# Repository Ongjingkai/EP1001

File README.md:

# EP1001
Just do things before they start to save you the time and effort

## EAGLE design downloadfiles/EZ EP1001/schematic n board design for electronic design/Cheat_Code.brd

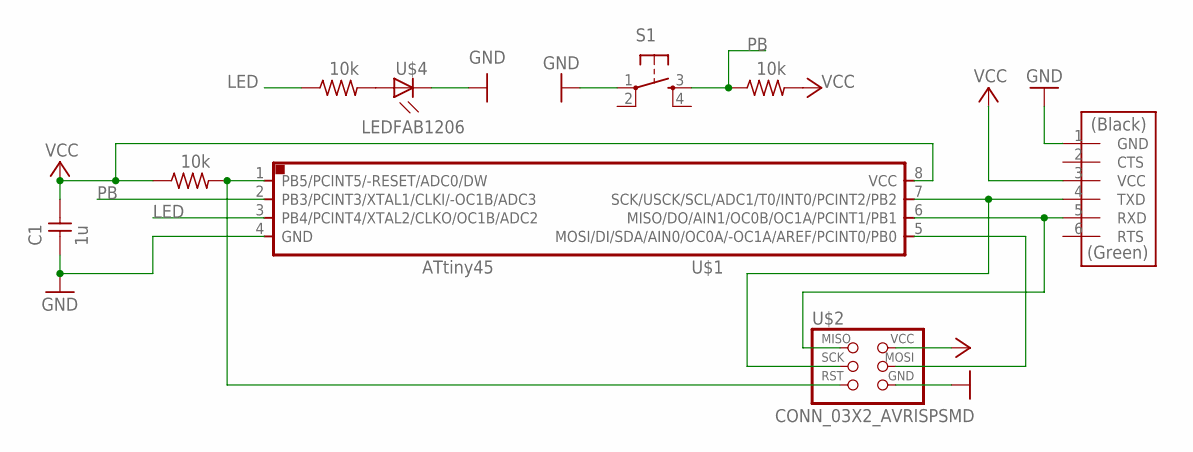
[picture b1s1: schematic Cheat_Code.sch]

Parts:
C1: 1u; C1206FAB
R1, R2, R3: 10k; R1206
S1: SW_SWITCH_TACTILE_6MM6MM_SWITCH; 6MM_SWITCH
U$1: UC_ATTINY45SI; SOIC8
U$2: CONN_03X2_AVRISPSMD; 2X03SMD
U$3: CONN_06_FTDI-SMD-HEADER; 1X06SMD
U$4: LEDFAB1206; LED1206FAB

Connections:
GND: C1.1, S1.1, U$1.4 (GND), U$2.6 (GND), U$3.1 (GND), U$4.2 (C)
LED: R3.1, U$1.3 (PB4/PCINT4/XTAL2/CLKO/OC1B/ADC2)
unnamed: U$1.6 (MISO/DO/AIN1/OC0B/OC1A/PCINT1/PB1), U$2.1 (MISO), U$3.5 (RXD)
unnamed: U$1.7 (SCK/USCK/SCL/ADC1/T0/INT0/PCINT2/PB2), U$2.3 (SCK), U$3.4 (TXD)
unnamed: R2.2, U$1.1 (PB5/PCINT5/-RESET/ADC0/DW), U$2.5 (RST)
unnamed: U$1.5 (MOSI/DI/SDA/AIN0/OC0A/-OC1A/AREF/PCINT0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), U$2.4 (MOSI)
unnamed: R3.2, U$4.1 (A)
PB: R1.1, S1.3 (S), U$1.2 (PB3/PCINT3/XTAL1/CLKI/-OC1B/ADC3)
VCC: C1.2, R1.2, R2.1, U$1.8 (VCC), U$2.2 (VCC), U$3.3 (VCC)

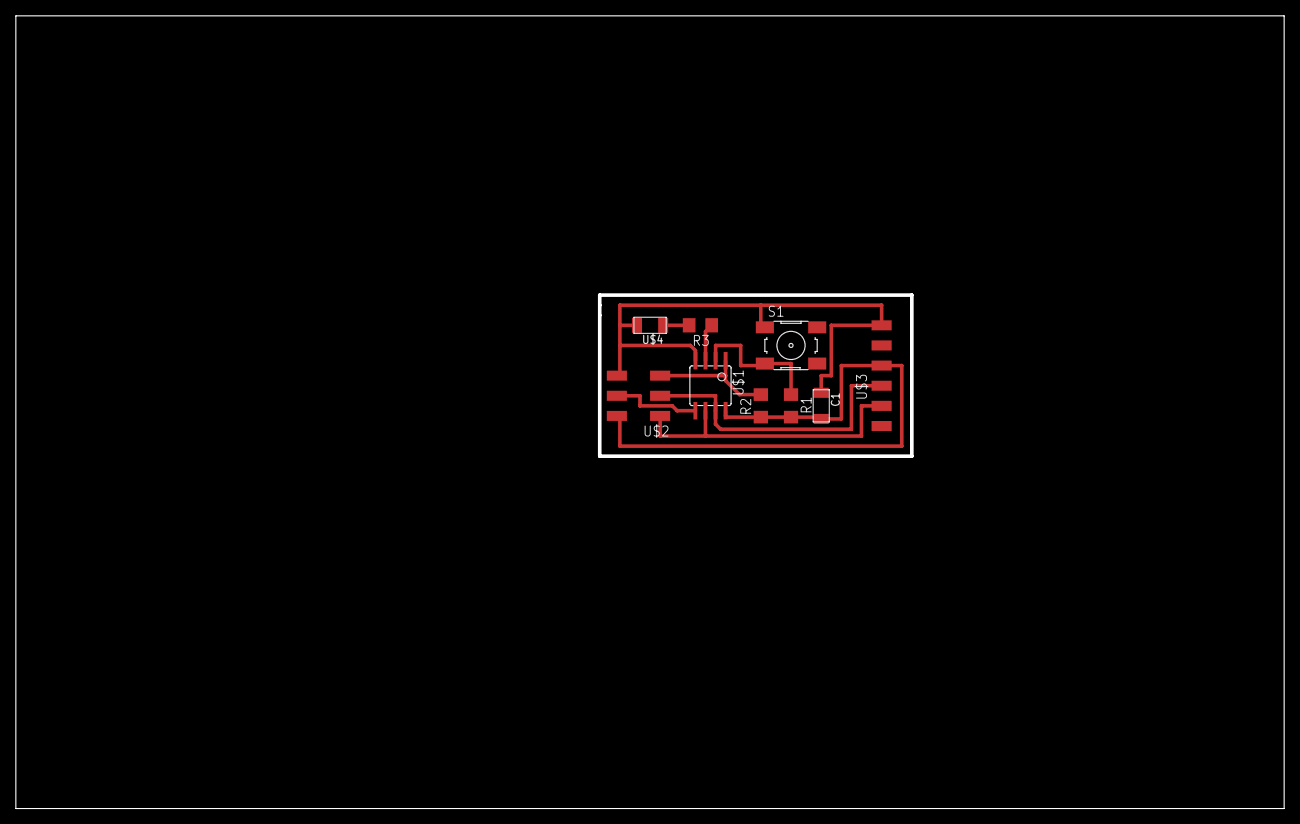
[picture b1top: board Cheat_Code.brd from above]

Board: 2 copper layers, 160.0 x 100.0 mm, 9 parts (0 on the bottom side), 9 nets.

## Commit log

2022-05-15 The Start of it all
2022-05-16 fablab safety shit
2022-10-05 deez
    nutz
2022-10-14 lazy mode
2022-10-21 Added Download files
2022-10-28 Slight update
2022-10-29 added soldering to electronic production
2022-10-30 Finished electronic production
2022-11-10 Added milled PCB in
2022-11-14 location error
2022-12-03 Updated 2d machining
    Among Us
2022-12-03 Bug fix with photo
2022-12-04 annoying naming issues
2022-12-10 bruh
2022-12-10 Finished VS code
2022-12-10 bug fix
2022-12-10 this is getting really annoying
2022-12-10 COMEON
2022-12-10 Updated embedded programming
2022-12-10 Updated VC
2022-12-10 grammar issue
2022-12-16 Finished embedded programming
2022-12-20 Finished 2dCNC
2023-01-11 updated molding and casting
    Added 3.0
2023-01-11 Update moldingandcasting.html
    Added work area
2023-01-11 updated file
2023-01-13 What's sleep am I right?
    Added photos and edited some smelly mistake
2023-01-25 Completed molding and casting
    finished molding and casting
    adding interface programming
2023-01-27 spelling mistake
2023-02-05 Updated interface programming
    Only thing left to update is the final results
2023-02-08 Completed interface programming
2023-02-18 Started on final project
2023-02-23 Normal final project update
2023-02-23 Finished 3d printed
2023-02-23 Completed cnc and laser cut
2023-02-23 Completed Showcase
    Read the name Please
2023-02-23 reeee
2023-02-23 almost complete assembly
2023-02-23 Issue ah this shit
2023-02-25 Finished interface programming
2023-02-26 quickly
2023-02-26 speed run
2023-02-27 Updated slide show
2023-02-27 Performing all final updates
